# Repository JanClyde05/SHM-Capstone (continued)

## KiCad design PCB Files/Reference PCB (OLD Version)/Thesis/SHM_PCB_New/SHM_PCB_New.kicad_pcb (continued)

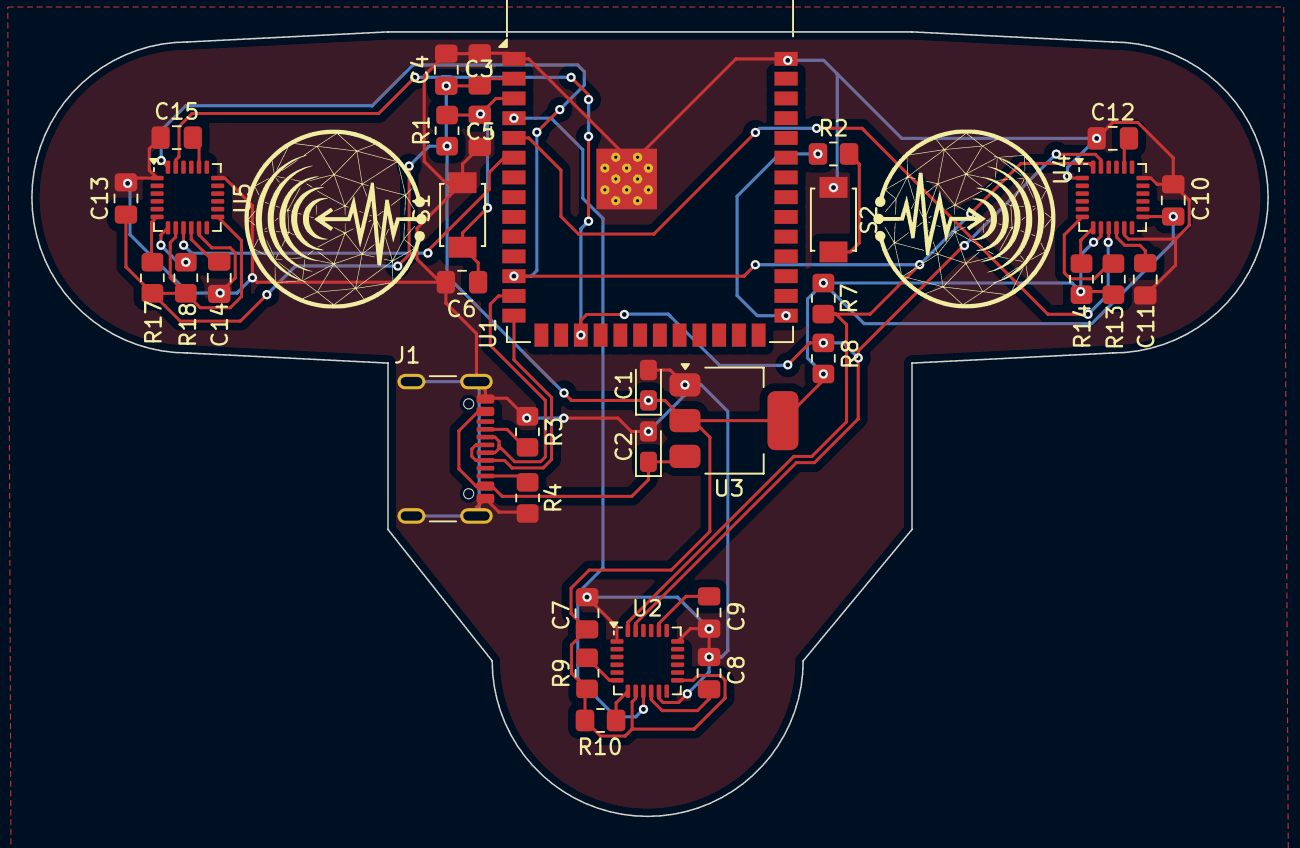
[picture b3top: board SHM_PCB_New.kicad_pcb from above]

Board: 2 copper layers, 79.5 x 50.5 mm, 36 parts (0 on the bottom side), 27 nets.

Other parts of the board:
*: LOGO

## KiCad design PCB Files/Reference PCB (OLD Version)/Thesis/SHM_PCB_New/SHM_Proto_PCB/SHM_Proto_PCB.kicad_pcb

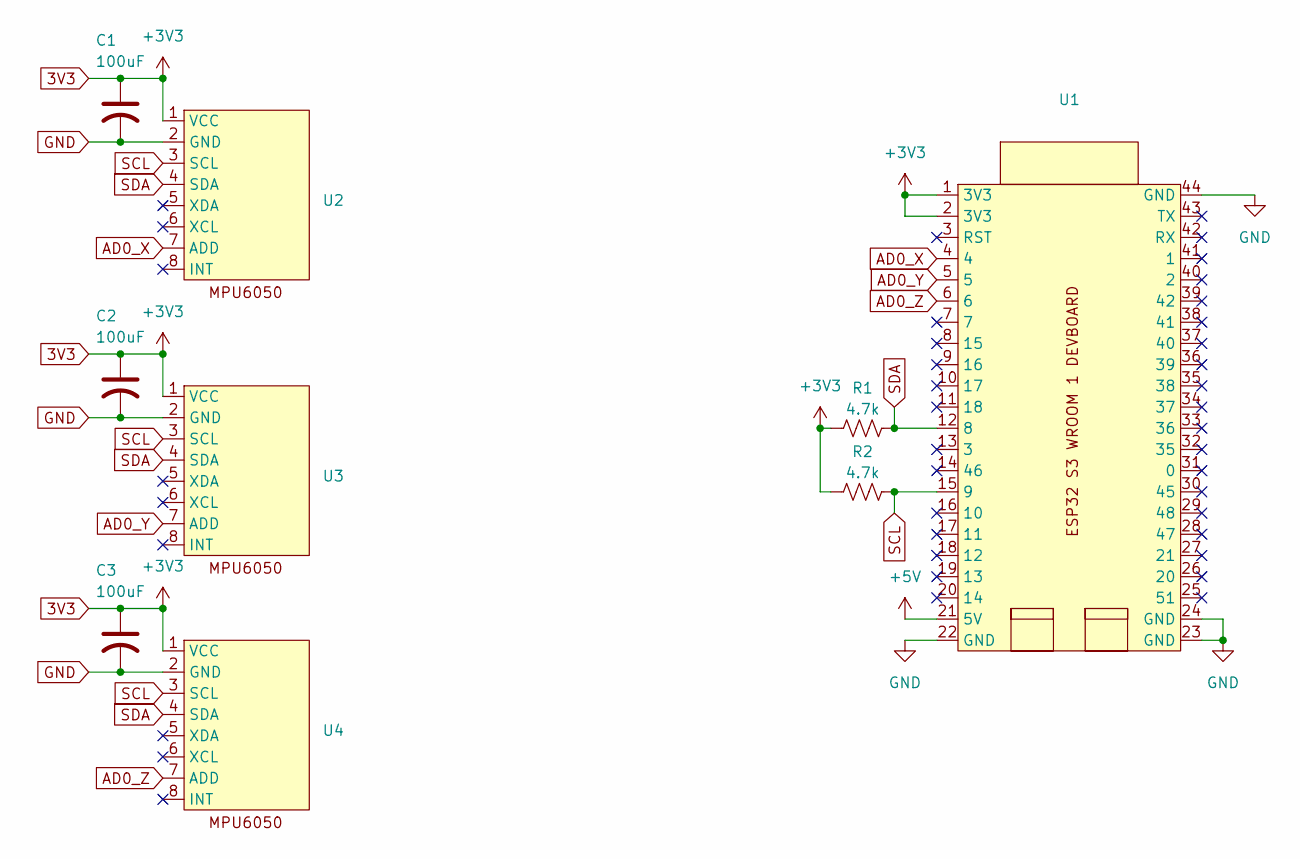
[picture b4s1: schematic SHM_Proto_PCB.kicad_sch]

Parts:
C1, C2, C3: 100uF; CP_Radial_D5.0mm_P2.00mm
R1, R2: 4.7k; R_Axial_DIN0309_L9.0mm_D3.2mm_P12.70mm_Horizontal
U1: ESP32 S3 WROOM 1 DEVBOARD
U2, U3, U4: MPU-6050

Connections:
3V3: C1.1, C2.1, C3.1, R1.1, R2.1, U1.1 (3V3), U1.2 (3V3), U2.1 (VCC), U3.1 (VCC), U4.1 (VCC)
+5V: U1.21 (5V)
AD0_X: U1.4, U2.7 (ADD)
AD0_Y: U1.5, U3.7 (ADD)
AD0_Z: U1.6, U4.7 (ADD)
GND: C1.2, C2.2, C3.2, U1.22 (GND), U1.23 (GND), U1.24 (GND), U1.44 (GND), U2.2 (GND), U3.2 (GND), U4.2 (GND)
SCL: R2.2, U1.15 (9), U2.3 (SCL), U3.3 (SCL), U4.3 (SCL)
SDA: R1.2, U1.12 (8), U2.4 (SDA), U3.4 (SDA), U4.4 (SDA)

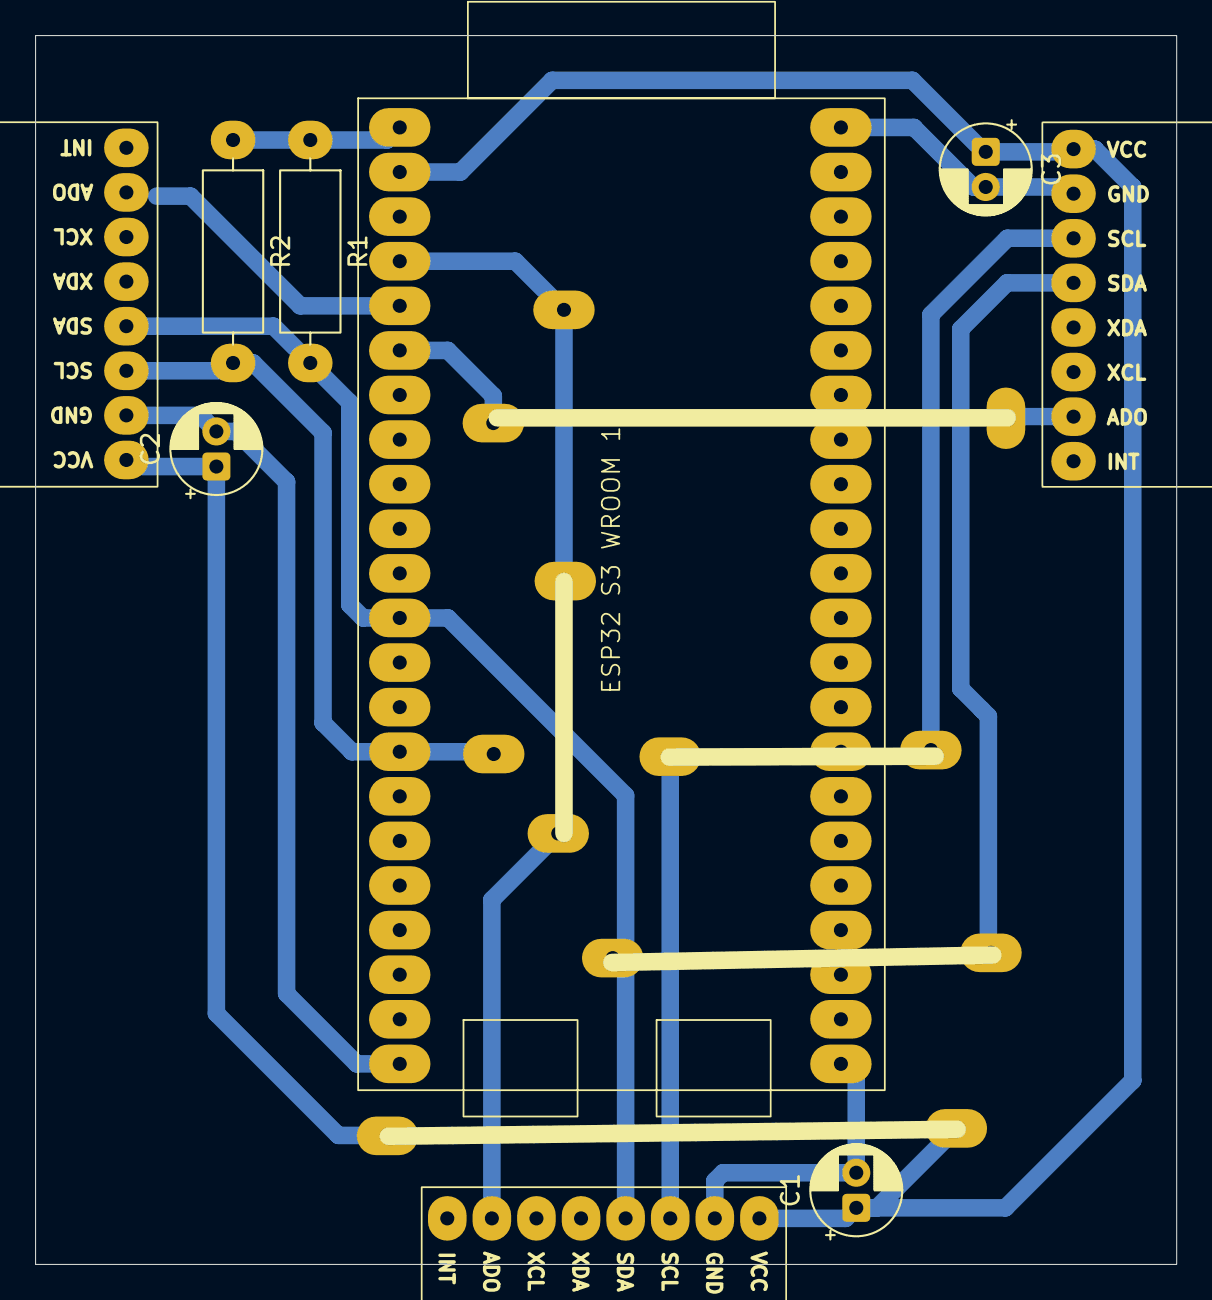
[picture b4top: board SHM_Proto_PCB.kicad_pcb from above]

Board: 2 copper layers, 65.0 x 70.0 mm, 9 parts (0 on the bottom side), 7 nets.
